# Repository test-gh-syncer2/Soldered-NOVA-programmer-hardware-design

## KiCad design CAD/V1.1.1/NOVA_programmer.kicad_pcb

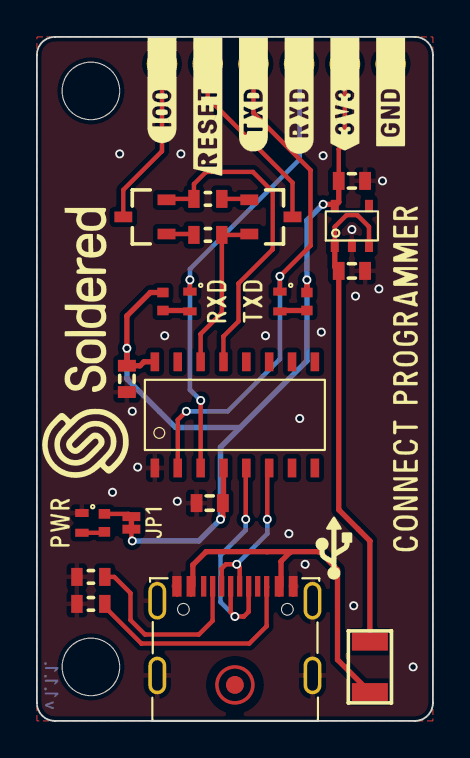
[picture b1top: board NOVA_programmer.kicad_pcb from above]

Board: 2 copper layers, 22.0 x 38.0 mm, 25 parts (1 on the bottom side), 20 nets.

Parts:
C1, C2: 0.1uF; 0603C
C3, C4: 2.2uF; 0603C
D1: white; 0402LED
D2: blue; 0402LED
D3: purple; 0402LED
F1: 1206FUSE-500mA; 1206FUSE
FD1: FIDUCIAL; FIDUCIAL_23
H1, H2: HOLE_3.2mm
JP1: SMD-JUMPER-CONNECTED_TRACE_SLODERMASK
K1: U262-161N-4BVC11
K2: NOVA_programmer_header; HEADER_MALE_6X1
Q1, Q2: NPN-SOT-23-3; SOT-23-3
R1, R2: 5.1k; 0603R
R3, R4: 10k; 0402R
R5: 2k2; 0402R
R6, R7: 10k; 0603R
U1: CH340C; SOP-16
U2: SE5218; SOT-23-5

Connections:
+3V3: C1.2, C2.1, C4.2, JP1.1, K2.2 (VCC), R3.2, R4.2, U1.4 (V3), U1.16 (VCC), U2.5 (VOUT)
D+: K1.A6 (DP1), K1.B6 (DP2), U1.5 (UD+)
D-: K1.A7 (DN1), K1.B7 (DN2), U1.6 (UD-)
DTR: Q2.2 (E), R6.1, U1.13 (DTR#)
GND: C1.1, C2.2, C3.1, C4.1, D3.2 (K), K1.A1 (GND), K1.A12 (GND), K1.B1 (GND), K1.B12 (GND), K1.SH (SHIELD), K2.1 (GND), R1.2, R2.2, U1.1 (GND), U2.2 (GND)
IO0: K2.6 (GPIO0), Q2.3 (C)
unnamed: D1.1 (A), R3.1
unnamed: D2.1 (A), R4.1
unnamed: D3.1 (A), R5.2
unnamed: F1.2, K1.A4 (VBUS), K1.A9 (VBUS), K1.B4 (VBUS), K1.B9 (VBUS)
unnamed: JP1.2, R5.1
unnamed: K1.A5 (CC1), R2.1
unnamed: K1.B5 (CC2), R1.1
unnamed: Q1.1 (B), R6.2
unnamed: Q2.1 (B), R7.2
RESET: K2.5 (RESET), Q1.3 (C)
RTS: Q1.2 (E), R7.1, U1.14 (RTS#)
RXD0: D2.2 (K), K2.3 (TX), U1.3 (RXD)
TXD0: D1.2 (K), K2.4 (RX), U1.2 (TXD)
VUSB: C3.2, F1.1, U2.1 (VIN), U2.3 (EN)

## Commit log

2021-09-23 Syncing to git
2021-09-23 Updating open source files.
